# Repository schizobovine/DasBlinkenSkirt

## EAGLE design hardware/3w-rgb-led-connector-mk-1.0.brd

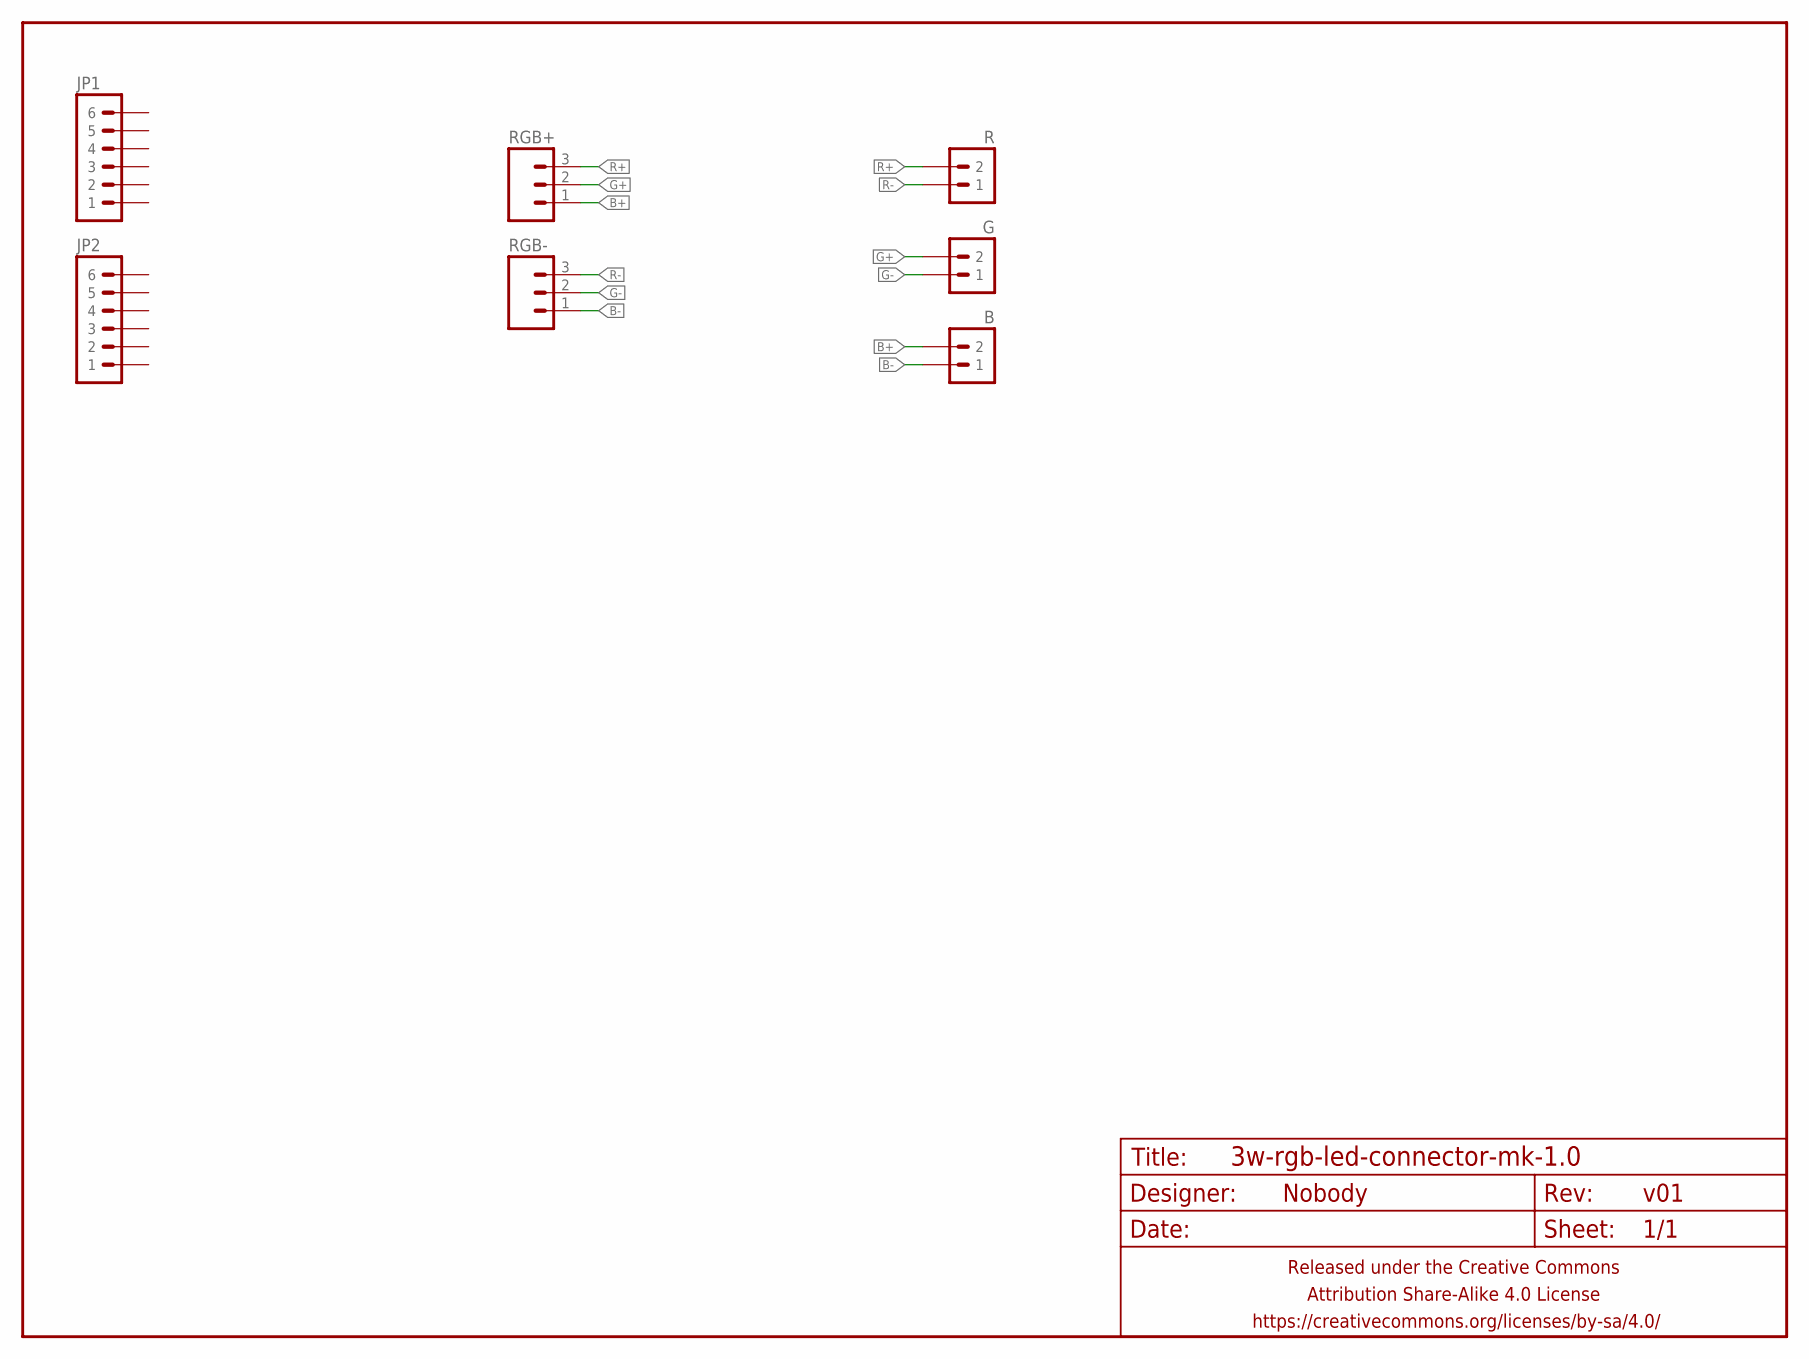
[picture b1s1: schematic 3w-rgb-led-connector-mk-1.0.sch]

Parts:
B: M023.5MM-NO_SILK; SCREWTERMINAL-3.5MM-2-NS
FRAME1: FRAME-LETTERNO_PACKAGE; DUMMY
G: M023.5MM-NO_SILK; SCREWTERMINAL-3.5MM-2-NS
JP1, JP2: M06SIP; 1X06
R: M023.5MM-NO_SILK; SCREWTERMINAL-3.5MM-2-NS
RGB+: M03JST-XH-RA-PTH; JST-3-XH-RA-PTH
RGB-: M03JST-XH-RA-PTH; JST-3-XH-RA-PTH

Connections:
B+: B.2, RGB+.1
B-: B.1, RGB-.1
G+: G.2, RGB+.2
G-: G.1, RGB-.2
R+: R.2, RGB+.3
R-: R.1, RGB-.3

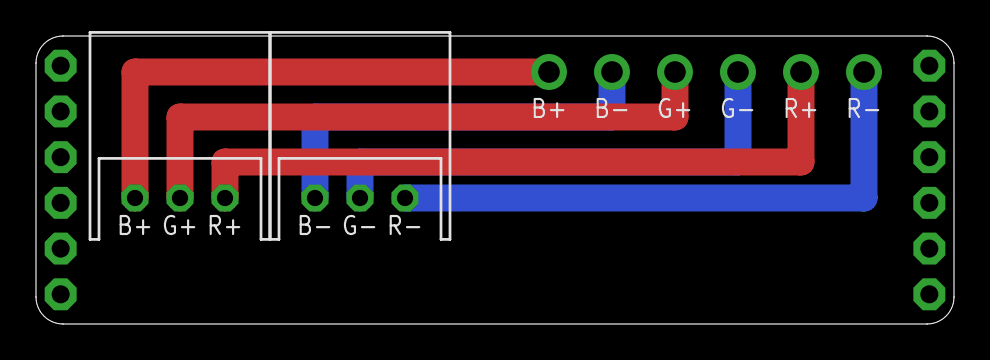
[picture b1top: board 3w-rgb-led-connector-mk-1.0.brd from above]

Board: 2 copper layers, 51.0 x 16.0 mm, 8 parts (0 on the bottom side), 6 nets.

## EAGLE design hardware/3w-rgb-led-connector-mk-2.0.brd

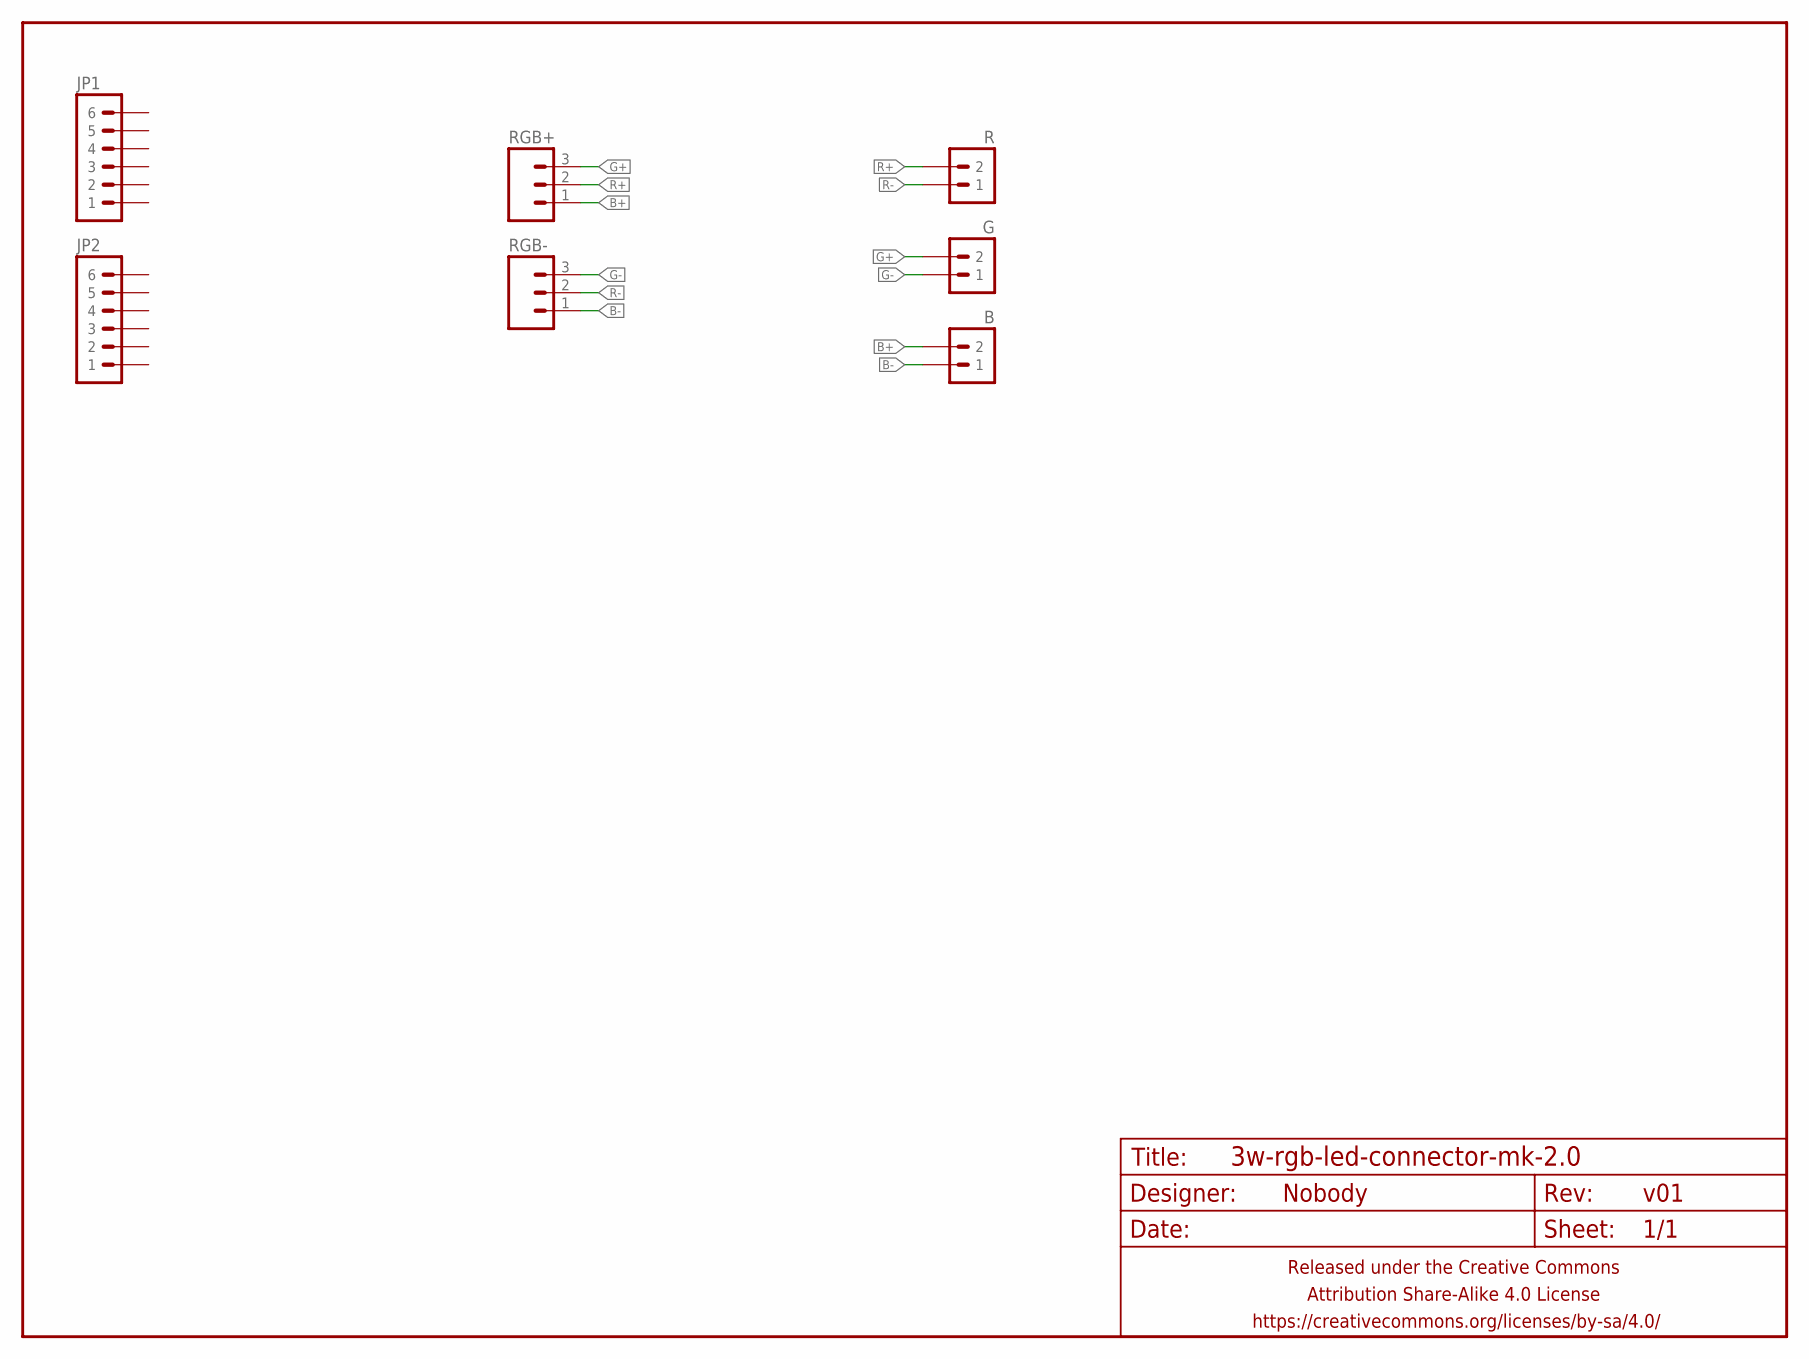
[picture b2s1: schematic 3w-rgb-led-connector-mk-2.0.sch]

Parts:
B: M023.5MM-NO_SILK; SCREWTERMINAL-3.5MM-2-NS
FRAME1: FRAME-LETTERNO_PACKAGE; DUMMY
G: M023.5MM-NO_SILK; SCREWTERMINAL-3.5MM-2-NS
JP1, JP2: M06SIP; 1X06
R: M023.5MM-NO_SILK; SCREWTERMINAL-3.5MM-2-NS
RGB+: M03JST-XH-RA-PTH; JST-3-XH-RA-PTH
RGB-: M03JST-XH-RA-PTH; JST-3-XH-RA-PTH

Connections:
B+: B.2, RGB+.1
B-: B.1, RGB-.1
G+: G.2, RGB+.3
G-: G.1, RGB-.3
R+: R.2, RGB+.2
R-: R.1, RGB-.2

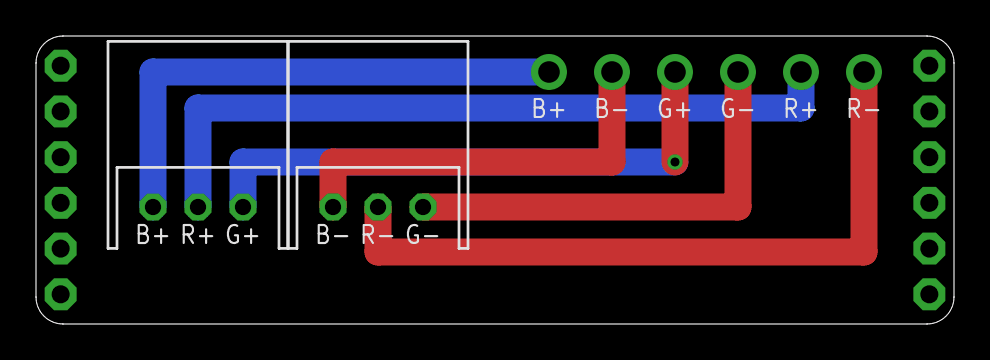
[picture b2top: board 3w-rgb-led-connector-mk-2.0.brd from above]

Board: 2 copper layers, 51.0 x 16.0 mm, 8 parts (0 on the bottom side), 6 nets.

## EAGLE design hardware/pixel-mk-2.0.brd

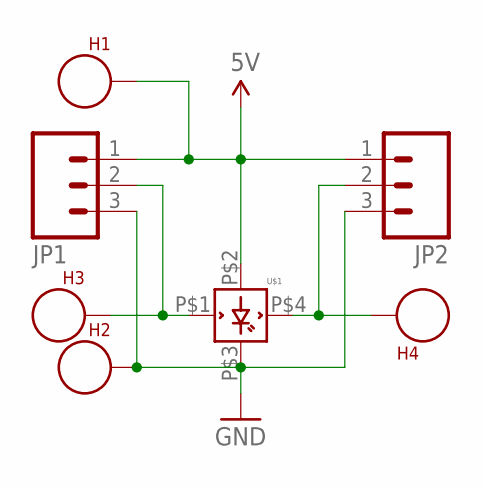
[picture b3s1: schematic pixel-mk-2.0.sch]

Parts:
H1, H2, H3, H4: SEW_HOLE; SIMPLE_HOLE
JP1, JP2: M03JST-PTH; JST-3-PTH
U$1: NEOPIXEL-PTH-5MM-CLEAR; LED-5MM-PTH-FUCK-RA

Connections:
5V: H1.P$1, JP1.1, JP2.1, U$1.P$2 (VDD)
GND: H2.P$1, JP1.3, JP2.3, U$1.P$3 (GND)
unnamed: H3.P$1, JP1.2, U$1.P$1 (DIN)
unnamed: H4.P$1, JP2.2, U$1.P$4 (DOUT)

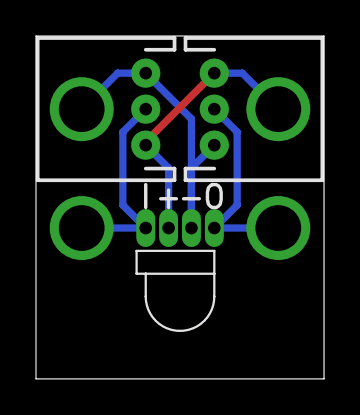
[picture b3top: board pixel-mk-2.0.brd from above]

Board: 2 copper layers, 16.0 x 19.1 mm, 7 parts (0 on the bottom side), 4 nets.

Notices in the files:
parts and their libraries:
A_butts: Released under the Creative Commons Attribution Share-Alike 4.0 License
A_butts: https://creativecommons.org/licenses/by-sa/4.0
A_butts: Released under the Creative Commons
